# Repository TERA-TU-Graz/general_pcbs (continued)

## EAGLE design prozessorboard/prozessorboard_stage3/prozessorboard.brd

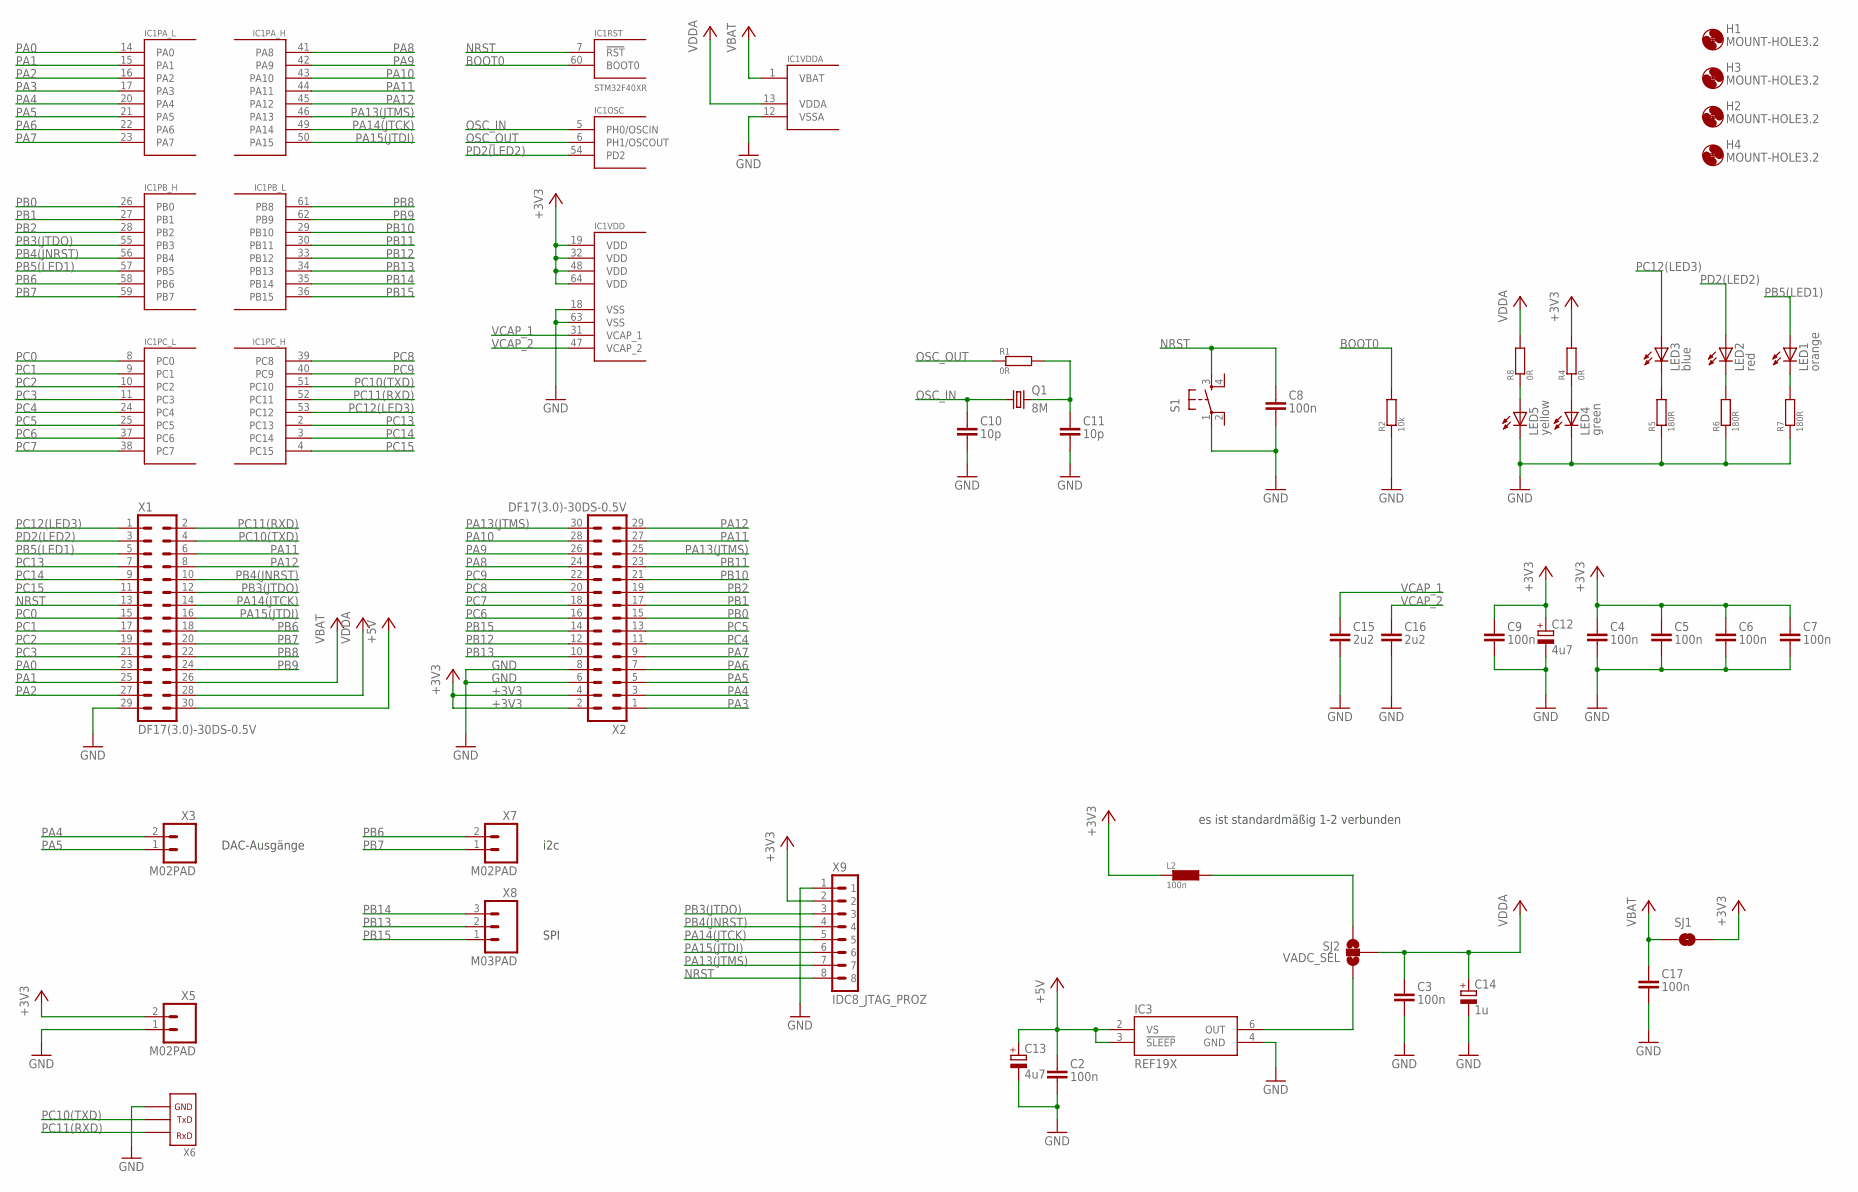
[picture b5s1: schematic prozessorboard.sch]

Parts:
C2, C3, C4, C5, C6, C7, C8, C9, C17: 100n; C0805
C10, C11: 10p; C0805
C12, C13: 4u7; CT3528
C14: 1u; CT3216
C15, C16: 2u2; C0805
H1, H2, H3, H4: MOUNT-HOLE3.2; 3,2
IC1: STM32F40XR; LQFP64
IC3: REF19X; SO08
L2: 100n; R0805
LED1: orange; CHIPLED_0805
LED2: red; CHIPLED_0805
LED3: blue; CHIPLED_0805
LED4: green; CHIPLED_0805
LED5: yellow; CHIPLED_0805
Q1: 8M; 0305
R1, R4, R8: 0R; R0805
R2: 10k; R0805
R5, R6, R7: 180R; R0805
S1: TAC_SWITCH; FSMJSMA
SJ1: SOLDERJUMPERNO; SJ_2S-NO
SJ2: VADC_SEL; SJ_3_PASTE1&2
X1, X2: DF17(3.0)-30DS-0.5V
X3, X5, X7: M02PAD; 1X02
X6: RS232V; 6410-03
X8: M03PAD; 1X03
X9: IDC8_JTAG_PROZ; 1X01

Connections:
+3V3: C4.2, C5.2, C6.2, C7.2, C9.2, C12.+, IC1.19 (VDD), IC1.32 (VDD), IC1.48 (VDD), IC1.64 (VDD), L2.1, R4.2, SJ1.2, X2.2, X2.4, X5.2, X9.2
+5V: C2.2, C13.+, IC3.2 (VS), IC3.3 (!SLEEP), X1.30
BOOT0: IC1.60 (BOOT0), R2.2
GND: C2.1, C3.1, C4.1, C5.1, C6.1, C7.1, C8.1, C9.1, C10.1, C11.1, C12.-, C13.-, C14.-, C15.1, C16.1, C17.1, IC1.12 (VSSA), IC1.18 (VSS), IC1.63 (VSS), IC3.4 (GND), LED4.C, LED5.C, R2.1, R5.1, R6.1, R7.1, S1.1, X1.29, X2.6, X2.8, X5.1, X6.1 (GND), X9.1
unnamed: C11.2, Q1.2, R1.2
unnamed: LED3.C, R5.2
unnamed: LED4.A, R4.1
unnamed: LED2.C, R6.2
unnamed: LED1.C, R7.2
unnamed: IC3.6 (OUT), SJ2.3
unnamed: LED5.A, R8.1
unnamed: L2.2, SJ2.1
NRST: C8.2, IC1.7 (!RST), S1.3, X1.13, X9.8
OSC_IN: C10.2, IC1.5 (PH0/OSCIN), Q1.1
OSC_OUT: IC1.6 (PH1/OSCOUT), R1.1
PA0: IC1.14 (PA0), X1.23
PA1: IC1.15 (PA1), X1.25
PA2: IC1.16 (PA2), X1.27
PA3: IC1.17 (PA3), X2.1
PA4: IC1.20 (PA4), X2.3, X3.2
PA5: IC1.21 (PA5), X2.5, X3.1
PA6: IC1.22 (PA6), X2.7
PA7: IC1.23 (PA7), X2.9
PA8: IC1.41 (PA8), X2.24
PA9: IC1.42 (PA9), X2.26
PA10: IC1.43 (PA10), X2.28
PA11: IC1.44 (PA11), X1.6, X2.27
PA12: IC1.45 (PA12), X1.8, X2.29
PA13(JTMS): IC1.46 (PA13), X2.25, X2.30, X9.7
PA14(JTCK): IC1.49 (PA14), X1.14, X9.5
PA15(JTDI): IC1.50 (PA15), X1.16, X9.6
PB0: IC1.26 (PB0), X2.15
PB1: IC1.27 (PB1), X2.17
PB2: IC1.28 (PB2), X2.19
PB3(JTDO): IC1.55 (PB3), X1.12, X9.3
PB4(JNRST): IC1.56 (PB4), X1.10, X9.4
PB5(LED1): IC1.57 (PB5), LED1.A, X1.5
PB6: IC1.58 (PB6), X1.18, X7.2
PB7: IC1.59 (PB7), X1.20, X7.1
PB8: IC1.61 (PB8), X1.22
PB9: IC1.62 (PB9), X1.24
PB10: IC1.29 (PB10), X2.21
PB11: IC1.30 (PB11), X2.23
PB12: IC1.33 (PB12), X2.12
PB13: IC1.34 (PB13), X2.10, X8.2
PB14: IC1.35 (PB14), X8.3
PB15: IC1.36 (PB15), X2.14, X8.1
PC0: IC1.8 (PC0), X1.15
PC1: IC1.9 (PC1), X1.17
PC2: IC1.10 (PC2), X1.19
PC3: IC1.11 (PC3), X1.21
PC4: IC1.24 (PC4), X2.11
PC5: IC1.25 (PC5), X2.13
PC6: IC1.37 (PC6), X2.16
PC7: IC1.38 (PC7), X2.18
PC8: IC1.39 (PC8), X2.20
PC9: IC1.40 (PC9), X2.22
PC10(TXD): IC1.51 (PC10), X1.4, X6.2 (TXD)
PC11(RXD): IC1.52 (PC11), X1.2, X6.3 (RXD)
PC12(LED3): IC1.53 (PC12), LED3.A, X1.1
PC13: IC1.2 (PC13), X1.7
PC14: IC1.3 (PC14), X1.9
PC15: IC1.4 (PC15), X1.11
PD2(LED2): IC1.54 (PD2), LED2.A, X1.3
VBAT: C17.2, IC1.1 (VBAT), SJ1.1, X1.26
VCAP_1: C15.2, IC1.31 (VCAP_1)
VCAP_2: C16.2, IC1.47 (VCAP_2)
VDDA: C3.2, C14.+, IC1.13 (VDDA), R8.2, SJ2.2, X1.28

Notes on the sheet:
es ist standardmäßig 1-2 verbunden
DAC-Ausgänge
SPI
i2c

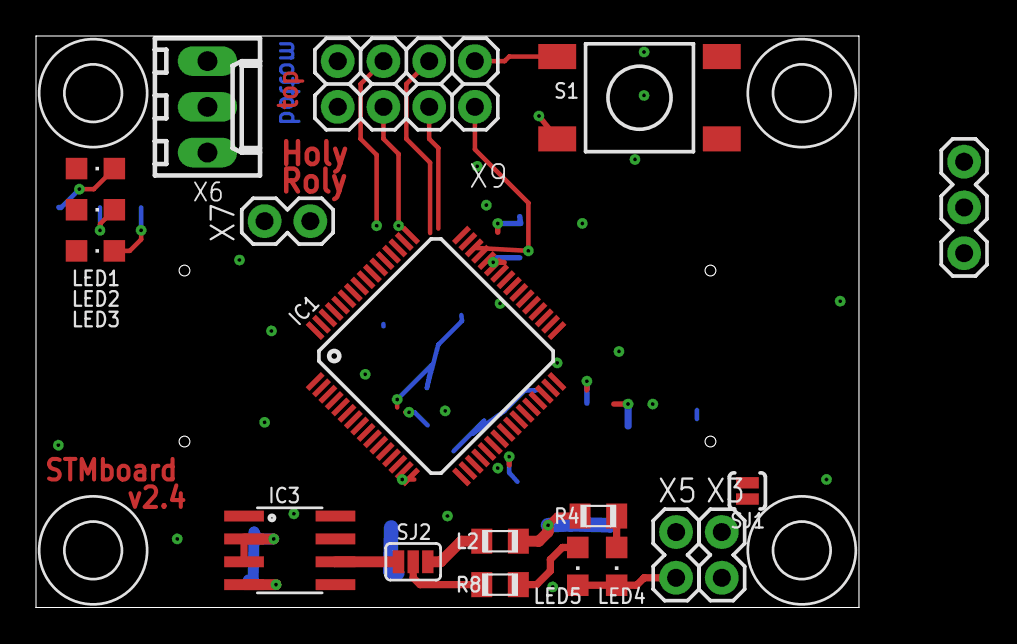
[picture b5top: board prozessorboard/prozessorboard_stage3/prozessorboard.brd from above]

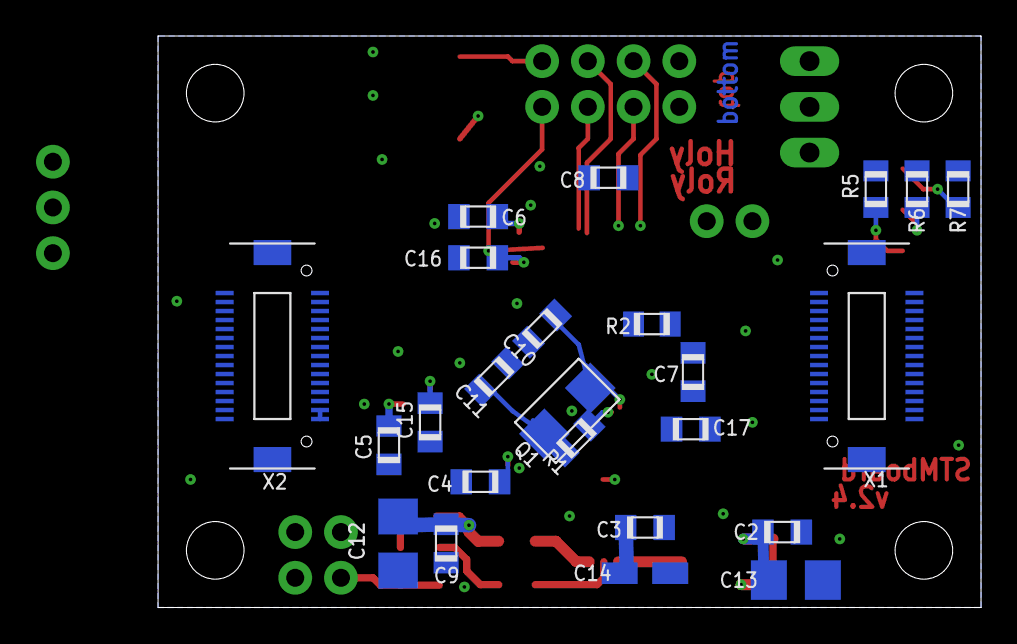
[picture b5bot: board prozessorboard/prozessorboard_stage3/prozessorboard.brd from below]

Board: 4 copper layers, 45.7 x 31.8 mm, 47 parts (24 on the bottom side), 68 nets.

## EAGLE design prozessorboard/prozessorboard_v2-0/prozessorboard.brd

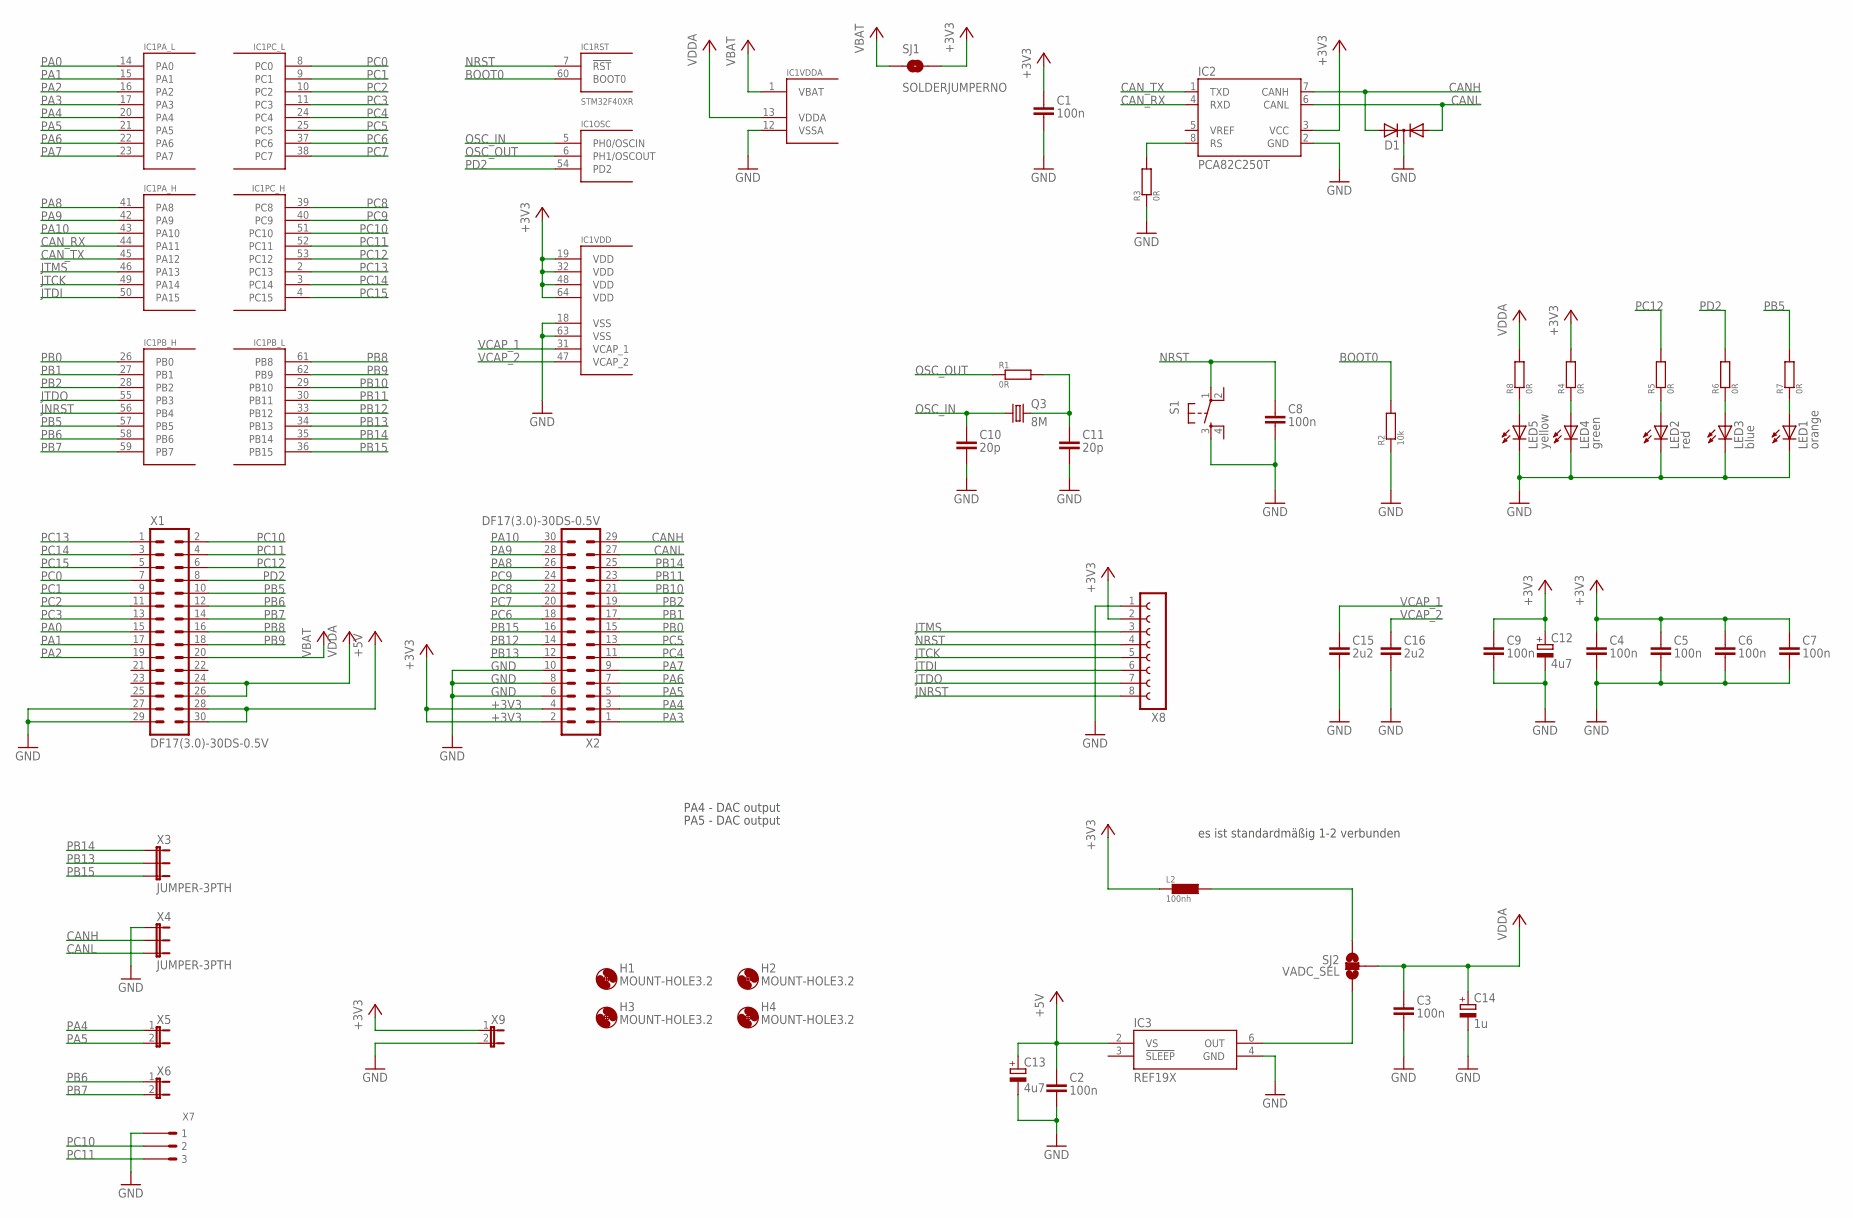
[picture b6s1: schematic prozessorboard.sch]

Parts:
C1, C2, C3, C4, C5, C6, C7, C8, C9: 100n; C0805
C10, C11: 20p; C0805
C12, C13: 4u7; SMC_C
C14: 1u; SMC_A
C15, C16: 2u2; C0805
D1: DIODE-2AC|CASOT23; SOT23
H1, H2, H3, H4: MOUNT-HOLE3.2; 3,2
IC1: STM32F40XR; LQFP64
IC2: PCA82C250T; SOIC-8
IC3: REF19X; SO08
L2: 100nh; R0805
LED1: orange; CHIPLED_0805
LED2: red; CHIPLED_0805
LED3: blue; CHIPLED_0805
LED4: green; CHIPLED_0805
LED5: yellow; CHIPLED_0805
Q3: 8M; 0305
R1, R3, R4, R5, R6, R7, R8: 0R; R0805
R2: 10k; R0805
S1: TAC_SWITCH; FSMJSMA
SJ1: SOLDERJUMPERNO; SJ_2S-NO
SJ2: VADC_SEL; SJ_3_PASTE1&2
X1, X2: DF17(3.0)-30DS-0.5V
X3, X4: JUMPER-3PTH; 1X03
X5, X6, X9: JUMPER-2PTH; 1X02
X7: 22-33; 6410-03
X8: FE08-1; FE08

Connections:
+3V3: C1.2, C4.2, C5.2, C6.2, C7.2, C9.2, C12.+, IC1.19 (VDD), IC1.32 (VDD), IC1.48 (VDD), IC1.64 (VDD), IC2.3 (VCC), L2.1, R4.2, SJ1.2, X2.2, X2.4, X8.2, X9.1
+5V: C2.2, C13.+, IC3.2 (VS), X1.28, X1.30
BOOT0: IC1.60 (BOOT0), R2.2
CANH: D1.2 (A2), IC2.7 (CANH), X2.29, X4.2
CANL: D1.1 (A1), IC2.6 (CANL), X2.27, X4.3
CAN_RX: IC1.44 (PA11), IC2.4 (RXD)
CAN_TX: IC1.45 (PA12), IC2.1 (TXD)
GND: C1.1, C2.1, C3.1, C4.1, C5.1, C6.1, C7.1, C8.1, C9.1, C10.1, C11.1, C12.-, C13.-, C14.-, C15.1, C16.1, D1.3 (C), IC1.12 (VSSA), IC1.18 (VSS), IC1.63 (VSS), IC2.2 (GND), IC3.4 (GND), LED1.C, LED2.C, LED3.C, LED4.C, LED5.C, R2.1, R3.1, S1.3, X1.27, X1.29, X2.6, X2.8, X2.10, X4.1, X7.1, X8.1, X9.2
JNRST: IC1.56 (PB4), X8.8
JTCK: IC1.49 (PA14), X8.5
JTDI: IC1.50 (PA15), X8.6
JTDO: IC1.55 (PB3), X8.7
JTMS: IC1.46 (PA13), X8.3
unnamed: C11.2, Q3.2, R1.2
unnamed: LED1.A, R7.1
unnamed: LED4.A, R4.1
unnamed: LED2.A, R5.1
unnamed: LED3.A, R6.1
unnamed: IC2.8 (RS), R3.2
unnamed: IC3.6 (OUT), SJ2.3
unnamed: LED5.A, R8.1
unnamed: L2.2, SJ2.1
NRST: C8.2, IC1.7 (!RST), S1.1, X8.4
OSC_IN: C10.2, IC1.5 (PH0/OSCIN), Q3.1
OSC_OUT: IC1.6 (PH1/OSCOUT), R1.1
PA0: IC1.14 (PA0), X1.15
PA1: IC1.15 (PA1), X1.17
PA2: IC1.16 (PA2), X1.19
PA3: IC1.17 (PA3), X2.1
PA4: IC1.20 (PA4), X2.3, X5.1
PA5: IC1.21 (PA5), X2.5, X5.2
PA6: IC1.22 (PA6), X2.7
PA7: IC1.23 (PA7), X2.9
PA8: IC1.41 (PA8), X2.26
PA9: IC1.42 (PA9), X2.28
PA10: IC1.43 (PA10), X2.30
PB0: IC1.26 (PB0), X2.15
PB1: IC1.27 (PB1), X2.17
PB2: IC1.28 (PB2), X2.19
PB5: IC1.57 (PB5), R7.2, X1.10
PB6: IC1.58 (PB6), X1.12, X6.1
PB7: IC1.59 (PB7), X1.14, X6.2
PB8: IC1.61 (PB8), X1.16
PB9: IC1.62 (PB9), X1.18
PB10: IC1.29 (PB10), X2.21
PB11: IC1.30 (PB11), X2.23
PB12: IC1.33 (PB12), X2.14
PB13: IC1.34 (PB13), X2.12, X3.2
PB14: IC1.35 (PB14), X2.25, X3.1
PB15: IC1.36 (PB15), X2.16, X3.3
PC0: IC1.8 (PC0), X1.7
PC1: IC1.9 (PC1), X1.9
PC2: IC1.10 (PC2), X1.11
PC3: IC1.11 (PC3), X1.13
PC4: IC1.24 (PC4), X2.11
PC5: IC1.25 (PC5), X2.13
PC6: IC1.37 (PC6), X2.18
PC7: IC1.38 (PC7), X2.20
PC8: IC1.39 (PC8), X2.22
PC9: IC1.40 (PC9), X2.24
PC10: IC1.51 (PC10), X1.2, X7.2
PC11: IC1.52 (PC11), X1.4, X7.3
PC12: IC1.53 (PC12), R5.2, X1.6
PC13: IC1.2 (PC13), X1.1
PC14: IC1.3 (PC14), X1.3
PC15: IC1.4 (PC15), X1.5
PD2: IC1.54 (PD2), R6.2, X1.8
VBAT: IC1.1 (VBAT), SJ1.1, X1.20
VCAP_1: C15.2, IC1.31 (VCAP_1)
VCAP_2: C16.2, IC1.47 (VCAP_2)
VDDA: C3.2, C14.+, IC1.13 (VDDA), R8.2, SJ2.2, X1.24, X1.26

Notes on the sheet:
PA4 - DAC output
PA5 - DAC output
es ist standardmäßig 1-2 verbunden

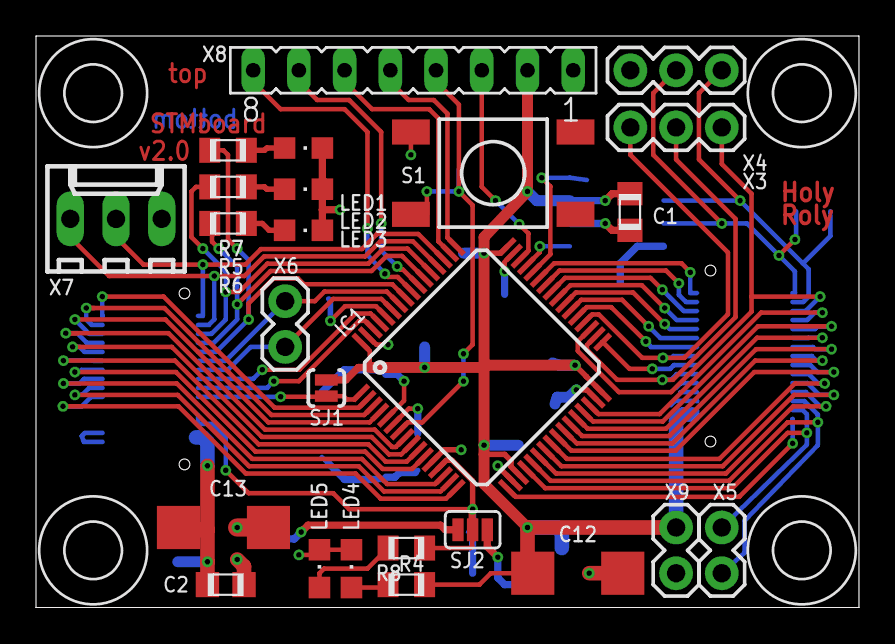
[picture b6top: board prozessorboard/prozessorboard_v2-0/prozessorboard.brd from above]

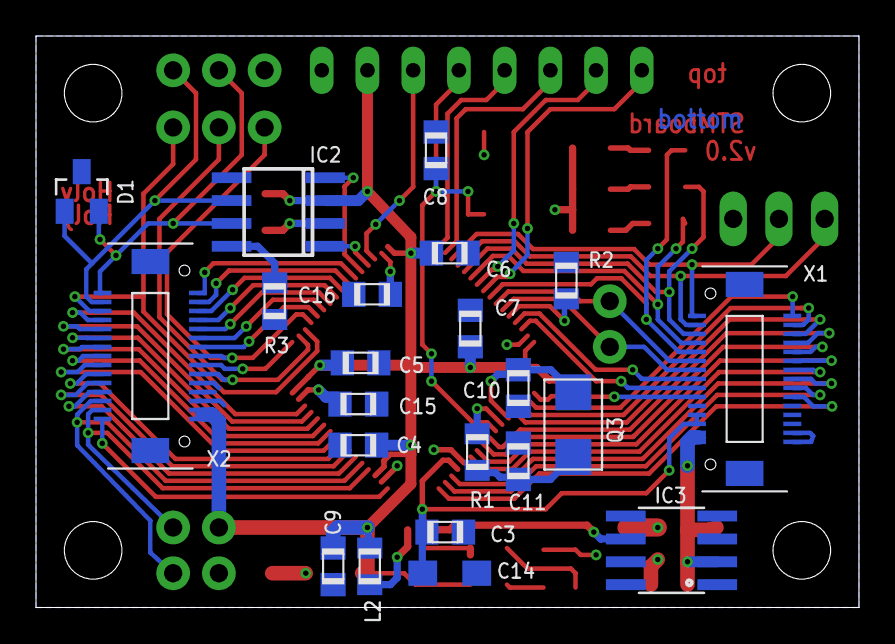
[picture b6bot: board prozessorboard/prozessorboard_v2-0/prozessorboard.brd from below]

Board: 2 copper layers, 45.7 x 31.8 mm, 51 parts (22 on the bottom side), 71 nets.

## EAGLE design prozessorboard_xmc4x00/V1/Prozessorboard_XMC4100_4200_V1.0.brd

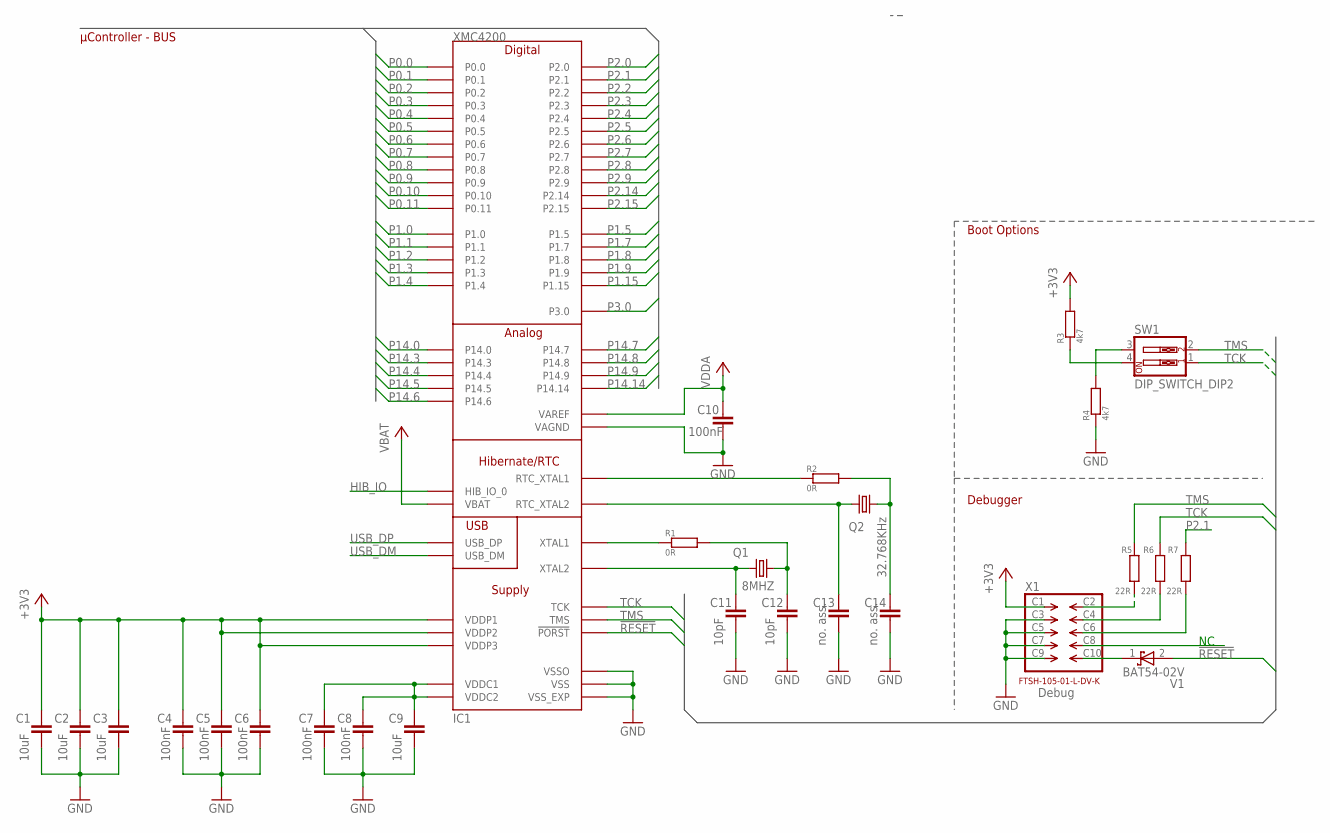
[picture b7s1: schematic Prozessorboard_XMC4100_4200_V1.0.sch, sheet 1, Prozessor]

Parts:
C1, C2, C3, C9: 10uF; C0805; MPN 1825002-1
C4, C5, C6, C7, C8, C10: 100nF; C0805
C11, C12: 10pF; C0805; MPN 1825002-1
C13, C14: no. ass.; C0805; MPN 1825002-1
IC1: XMC4200; INF-PG-LQFP-64-19-5800X5800T57PRIMARY
Q1: 8MHZ; 0305+1MM
Q2: 32.768KHz; 0305+1MM
R1, R2: 0R; R0805@1
R3, R4: 4k7; R0805@1
R5, R6, R7: 22R; R0805@1
SW1: DIP_SWITCH_DIP2; DIPSWITCH-02
V1: BAT54-02V; SC79
X1: Debug; SMD_10PIN_2ROW_1.27MM_SAMTEC

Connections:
!RESET: IC1.43 (!PORST), V1.2 (A); also elsewhere on the board
+3V3: C1.2, C2.2, C3.2, C4.2, C5.2, C6.2, IC1.8 (VDDP1), IC1.38 (VDDP2), IC1.56 (VDDP3), R3.2, X1.C1; also elsewhere on the board
GND: C1.1, C2.1, C3.1, C4.1, C5.1, C6.1, C7.1, C8.1, C9.1, C10.1, C11.1, C12.1, C13.1, C14.1, IC1.21 (VAGND), IC1.37 (VSS), IC1.41 (VSSO), IC1.65 (VSS_EXP), R4.1, X1.C3, X1.C5, X1.C7, X1.C9; also elsewhere on the board
HIB_IO: IC1.10 (HIB_IO_0); also elsewhere on the board
unnamed: C11.2, IC1.40 (XTAL2), Q1.2
unnamed: V1.1 (C), X1.C10
unnamed: IC1.39 (XTAL1), R1.1
unnamed: C7.2, C8.2, C9.2, IC1.9 (VDDC1), IC1.42 (VDDC2)
unnamed: C13.2, IC1.12 (RTC_XTAL2), Q2.2
unnamed: IC1.11 (RTC_XTAL1), R2.1
unnamed: C14.2, Q2.1, R2.2
unnamed: C12.2, Q1.1, R1.2
unnamed: R5.1, X1.C2
unnamed: R6.1, X1.C4
unnamed: R7.1, X1.C6
unnamed: R3.1, SW1.4
unnamed: R4.2, SW1.3
P0.0: IC1.2 (P0.0); also elsewhere on the board
P0.1: IC1.1 (P0.1); also elsewhere on the board
P0.2: IC1.64 (P0.2); also elsewhere on the board
P0.3: IC1.63 (P0.3); also elsewhere on the board
P0.4: IC1.62 (P0.4); also elsewhere on the board
P0.5: IC1.61 (P0.5); also elsewhere on the board
P0.6: IC1.60 (P0.6); also elsewhere on the board
P0.7: IC1.58 (P0.7); also elsewhere on the board
P0.8: IC1.57 (P0.8); also elsewhere on the board
P0.9: IC1.4 (P0.9); also elsewhere on the board
P0.10: IC1.3 (P0.10); also elsewhere on the board
P0.11: IC1.59 (P0.11); also elsewhere on the board
P1.0: IC1.52 (P1.0); also elsewhere on the board
P1.1: IC1.51 (P1.1); also elsewhere on the board
P1.2: IC1.50 (P1.2); also elsewhere on the board
P1.3: IC1.49 (P1.3); also elsewhere on the board
P1.4: IC1.48 (P1.4); also elsewhere on the board
P1.5: IC1.47 (P1.5); also elsewhere on the board
P1.7: IC1.55 (P1.7); also elsewhere on the board
P1.8: IC1.54 (P1.8); also elsewhere on the board
P1.9: IC1.53 (P1.9); also elsewhere on the board
P1.15: IC1.46 (P1.15); also elsewhere on the board
P2.0: IC1.34 (P2.0); also elsewhere on the board
P2.1: IC1.33 (P2.1), R7.2
P2.2: IC1.32 (P2.2); also elsewhere on the board
P2.3: IC1.31 (P2.3); also elsewhere on the board
P2.4: IC1.30 (P2.4); also elsewhere on the board
P2.5: IC1.29 (P2.5); also elsewhere on the board
P2.6: IC1.36 (P2.6); also elsewhere on the board
P2.7: IC1.35 (P2.7); also elsewhere on the board
P2.8: IC1.28 (P2.8); also elsewhere on the board
P2.9: IC1.27 (P2.9); also elsewhere on the board
P2.14: IC1.26 (P2.14); also elsewhere on the board
P2.15: IC1.25 (P2.15); also elsewhere on the board
P3.0: IC1.5 (P3.0); also elsewhere on the board
P14.0: IC1.20 (P14.0); also elsewhere on the board
P14.3: IC1.19 (P14.3); also elsewhere on the board
P14.4: IC1.18 (P14.4); also elsewhere on the board
P14.5: IC1.17 (P14.5); also elsewhere on the board
P14.6: IC1.16 (P14.6); also elsewhere on the board
P14.7: IC1.15 (P14.7); also elsewhere on the board
P14.8: IC1.24 (P14.8); also elsewhere on the board
P14.9: IC1.23 (P14.9); also elsewhere on the board
P14.14: IC1.14 (P14.14); also elsewhere on the board
TCK: IC1.45 (TCK), R6.2, SW1.1
TMS: IC1.44 (TMS), R5.2, SW1.2
USB_DM: IC1.6 (USB_DM); also elsewhere on the board
USB_DP: IC1.7 (USB_DP); also elsewhere on the board
VBAT: IC1.13 (VBAT); also elsewhere on the board
VDDA: C10.2, IC1.22 (VAREF); also elsewhere on the board

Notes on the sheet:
Debugger
Boot Options
µController - BUS

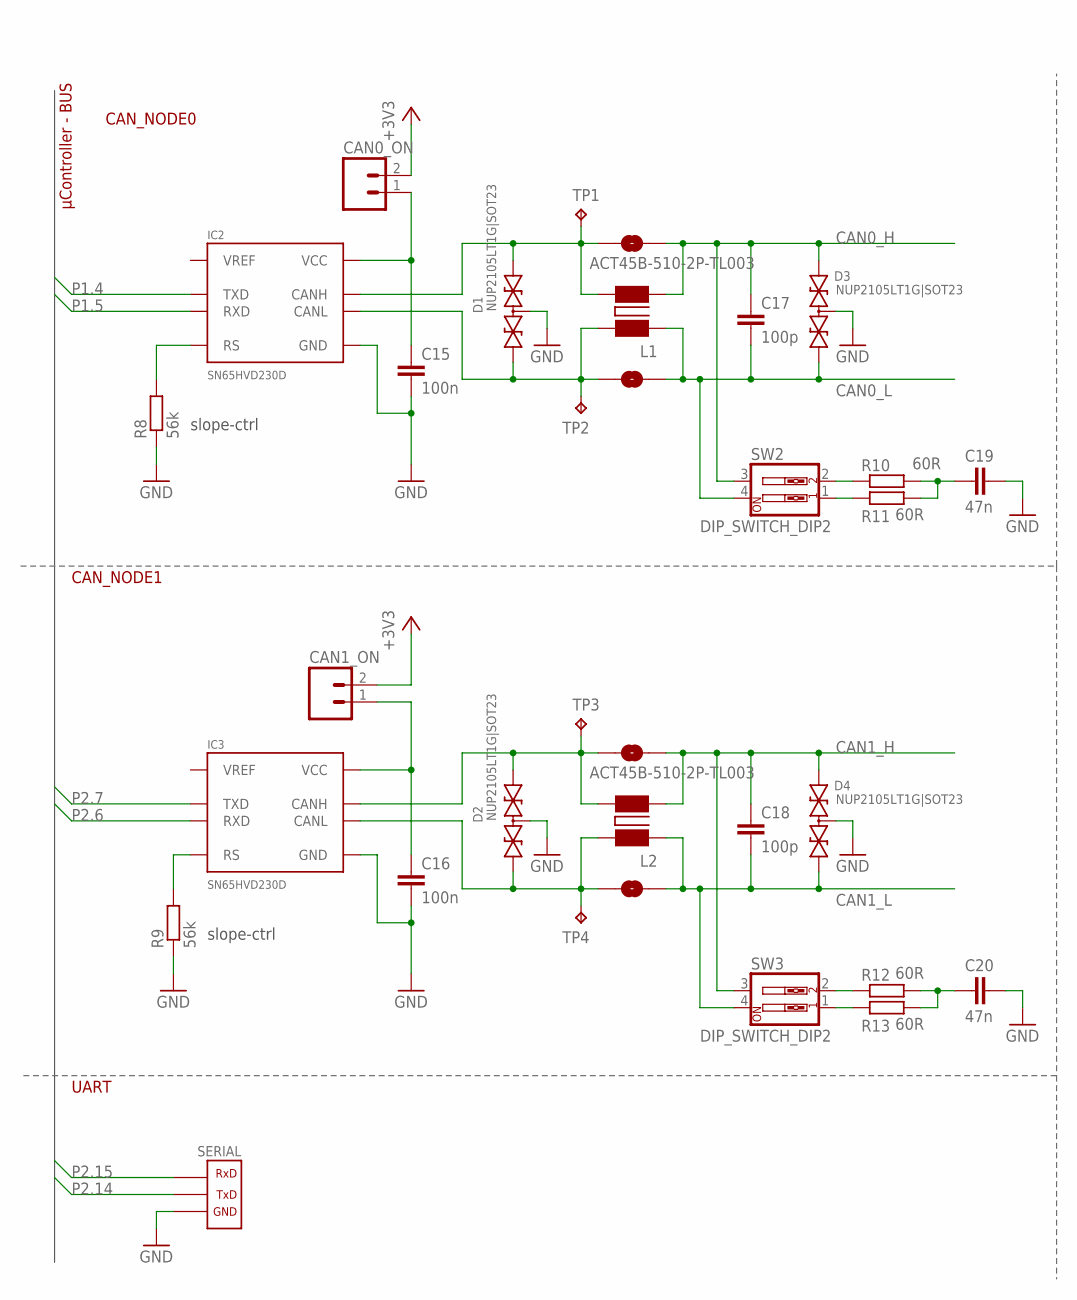
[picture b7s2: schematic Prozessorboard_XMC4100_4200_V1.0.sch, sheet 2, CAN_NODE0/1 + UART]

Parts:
C15, C16: 100n; C0805
C17, C18: 100p; C0805
C19, C20: 47n; C0805
CAN0_ON, CAN1_ON: M02PAD; 1X02
D1, D2, D3, D4: NUP2105LT1G|SOT23; SOT23
IC2, IC3: SN65HVD230D; SO08
L1, L2: ACT45B-510-2P-TL003; ACT45B
R8, R9: 56k; R0805
R10, R11, R12, R13: 60R; R0805
SERIAL: RS232V; 6410-03
SJ1, SJ2, SJ3, SJ4: SOLDERJUMPERNO; SJ_2S-NO
SW2, SW3: DIP_SWITCH_DIP2; DIPSWITCH-02
TP1, TP2, TP3, TP4: TPPAD1-13; P1-13

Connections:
+3V3: CAN0_ON.2, CAN1_ON.2; also elsewhere on the board
CAN0_H: C17.1, D3.2, L1.P$1 (1), SJ1.2, SW2.3; also elsewhere on the board
CAN0_L: C17.2, D3.1, L1.P$3 (3), SJ2.2, SW2.4; also elsewhere on the board
CAN1_H: C18.1, D4.2, L2.P$1 (1), SJ3.2, SW3.3; also elsewhere on the board
CAN1_L: C18.2, D4.1, L2.P$3 (3), SJ4.2, SW3.4; also elsewhere on the board
GND: C15.2, C16.2, C19.2, C20.2, D1.3, D2.3, D3.3, D4.3, IC2.2 (GND), IC3.2 (GND), R8.1, R9.1, SERIAL.1 (GND); also elsewhere on the board
unnamed: R10.1, SW2.2
unnamed: R12.1, SW3.2
unnamed: R13.1, SW3.1
unnamed: IC3.8 (RS), R9.2
unnamed: C16.1, CAN1_ON.1, IC3.3 (VCC)
unnamed: D2.2, IC3.7 (CANH), L2.P$2 (2), SJ3.1, TP3.TP
unnamed: C15.1, CAN0_ON.1, IC2.3 (VCC)
unnamed: D2.1, IC3.6 (CANL), L2.P$4 (4), SJ4.1, TP4.TP
unnamed: IC2.8 (RS), R8.2
unnamed: R11.1, SW2.1
unnamed: C19.1, R10.2, R11.2
unnamed: D1.2, IC2.7 (CANH), L1.P$2 (2), SJ1.1, TP1.TP
unnamed: D1.1, IC2.6 (CANL), L1.P$4 (4), SJ2.1, TP2.TP
unnamed: C20.1, R12.2, R13.2
P1.4: IC2.1 (TXD); also elsewhere on the board
P1.5: IC2.4 (RXD); also elsewhere on the board
P2.6: IC3.4 (RXD); also elsewhere on the board
P2.7: IC3.1 (TXD); also elsewhere on the board
P2.14: SERIAL.2 (TXD); also elsewhere on the board
P2.15: SERIAL.3 (RXD); also elsewhere on the board

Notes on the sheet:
CAN_NODE0
slope-ctrl
CAN_NODE1
µController - BUS
UART

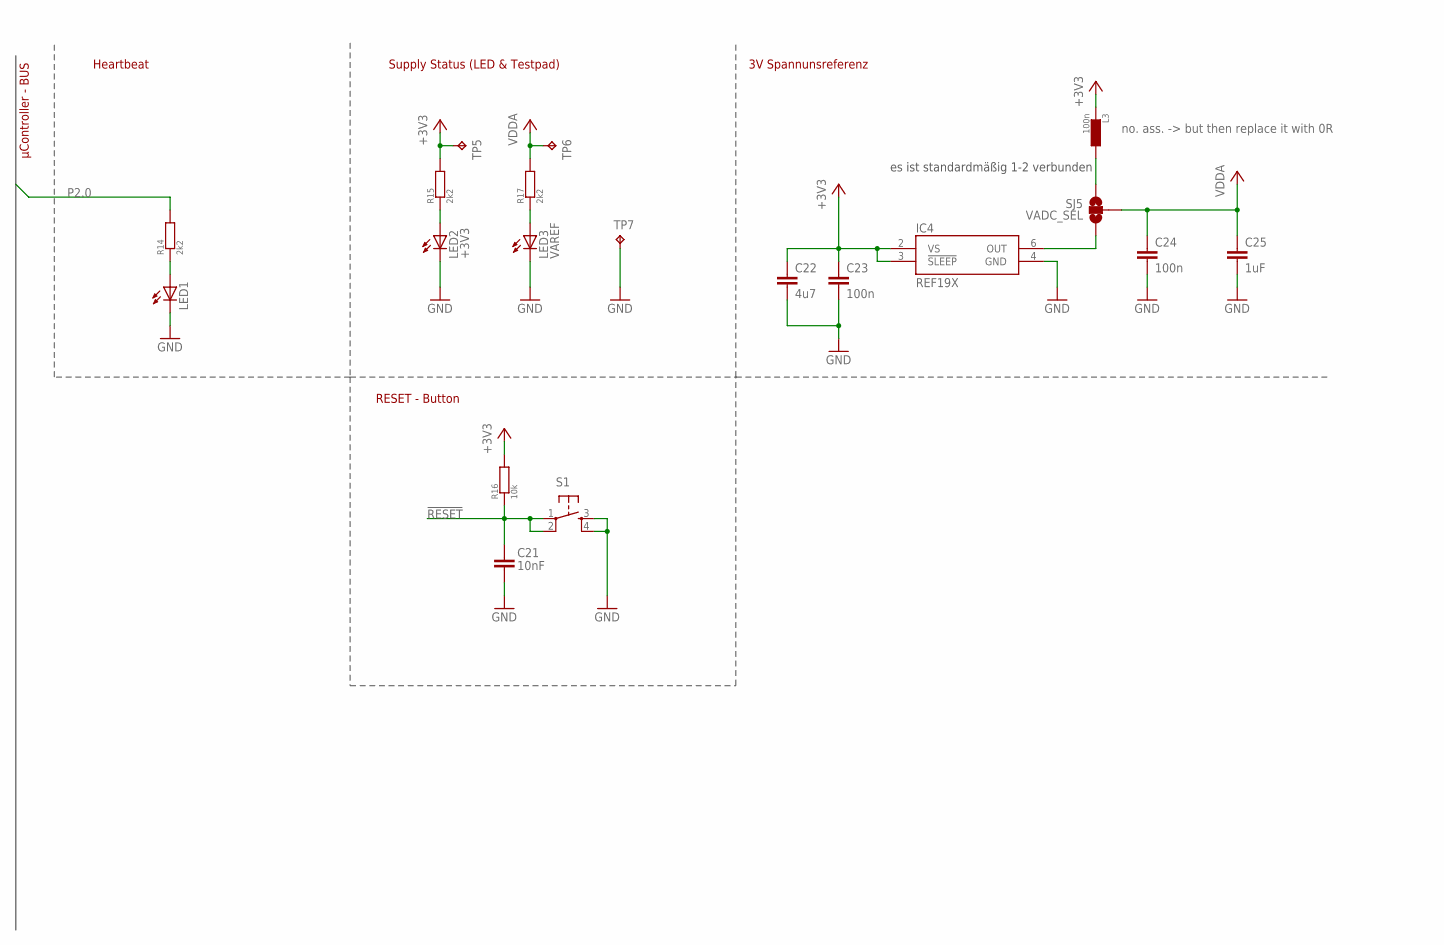
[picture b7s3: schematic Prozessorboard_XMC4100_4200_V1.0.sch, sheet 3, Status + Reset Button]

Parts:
C21: 10nF; C0805
C22: 4u7; 0805
C23, C24: 100n; 0805
C25: 1uF; 0805
IC4: REF19X; SO08
L3: 100n; R0805
LED1: LEDCHIPLED_0805; CHIPLED_0805
LED2: +3V3; CHIPLED_0805
LED3: VAREF; CHIPLED_0805
R14, R15, R17: 2k2; R0805@1
R16: 10k; R0805@1
S1: TAC_SWITCH; FSMJSMA
SJ5: VADC_SEL; SJ_3_PASTE1&2
TP5, TP6, TP7: TPPAD1-13; P1-13

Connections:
!RESET: C21.2, R16.1, S1.1, S1.2; also elsewhere on the board
+3V3: C22.1, C23.1, IC4.2 (VS), IC4.3 (!SLEEP), L3.1, R15.2, R16.2, TP5.TP; also elsewhere on the board
GND: C21.1, C22.2, C23.2, C24.2, C25.2, IC4.4 (GND), LED1.C, LED2.C, LED3.C, S1.3, S1.4, TP7.TP; also elsewhere on the board
unnamed: LED1.A, R14.1
unnamed: LED2.A, R15.1
unnamed: LED3.A, R17.1
unnamed: L3.2, SJ5.1
unnamed: IC4.6 (OUT), SJ5.3
P2.0: R14.2; also elsewhere on the board
VDDA: C24.1, C25.1, R17.2, SJ5.2, TP6.TP; also elsewhere on the board

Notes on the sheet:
Heartbeat
Supply Status (LED & Testpad)
RESET - Button
µController - BUS
es ist standardmäßig 1-2 verbunden
3V Spannunsreferenz
no. ass. -> but then replace it with 0R

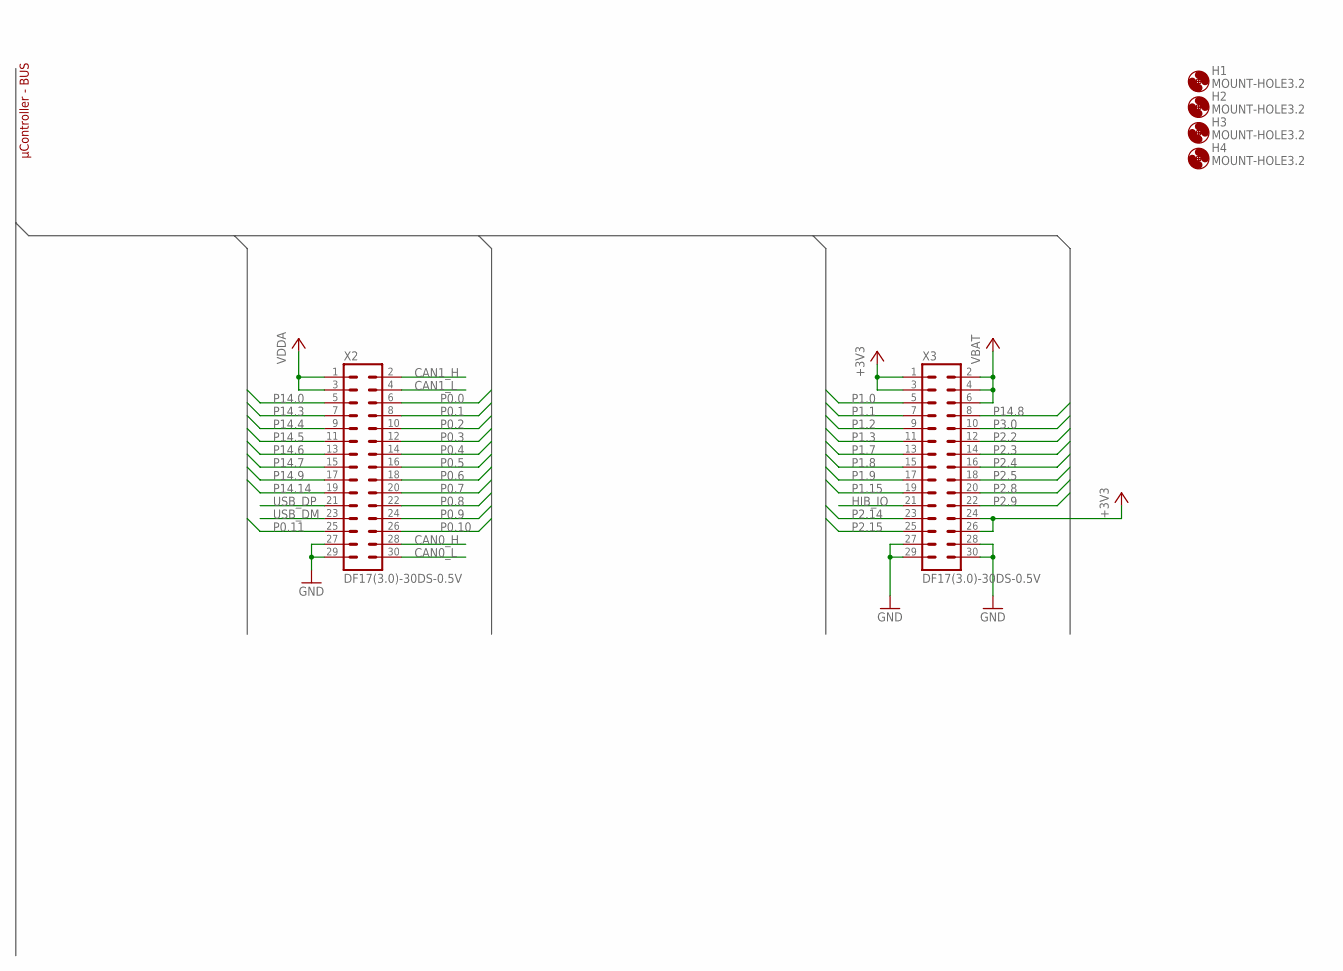
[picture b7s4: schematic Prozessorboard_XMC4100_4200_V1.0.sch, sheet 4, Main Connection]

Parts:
H1, H2, H3, H4: MOUNT-HOLE3.2; 3,2
X2, X3: DF17(3.0)-30DS-0.5V

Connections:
+3V3: X3.1, X3.3, X3.24, X3.26; also elsewhere on the board
CAN0_H: X2.28; also elsewhere on the board
CAN0_L: X2.30; also elsewhere on the board
CAN1_H: X2.2; also elsewhere on the board
CAN1_L: X2.4; also elsewhere on the board
GND: X2.27, X2.29, X3.27, X3.28, X3.29, X3.30; also elsewhere on the board
HIB_IO: X3.21; also elsewhere on the board
P0.0: X2.6; also elsewhere on the board
P0.1: X2.8; also elsewhere on the board
P0.2: X2.10; also elsewhere on the board
P0.3: X2.12; also elsewhere on the board
P0.4: X2.14; also elsewhere on the board
P0.5: X2.16; also elsewhere on the board
P0.6: X2.18; also elsewhere on the board
P0.7: X2.20; also elsewhere on the board
P0.8: X2.22; also elsewhere on the board
P0.9: X2.24; also elsewhere on the board
P0.10: X2.26; also elsewhere on the board
P0.11: X2.25; also elsewhere on the board
P1.0: X3.5; also elsewhere on the board
P1.1: X3.7; also elsewhere on the board
P1.2: X3.9; also elsewhere on the board
P1.3: X3.11; also elsewhere on the board
P1.7: X3.13; also elsewhere on the board
P1.8: X3.15; also elsewhere on the board
P1.9: X3.17; also elsewhere on the board
P1.15: X3.19; also elsewhere on the board
P2.2: X3.12; also elsewhere on the board
P2.3: X3.14; also elsewhere on the board
P2.4: X3.16; also elsewhere on the board
P2.5: X3.18; also elsewhere on the board
P2.8: X3.20; also elsewhere on the board
P2.9: X3.22; also elsewhere on the board
P2.14: X3.23; also elsewhere on the board
P2.15: X3.25; also elsewhere on the board
P3.0: X3.10; also elsewhere on the board
P14.0: X2.5; also elsewhere on the board
P14.3: X2.7; also elsewhere on the board
P14.4: X2.9; also elsewhere on the board
P14.5: X2.11; also elsewhere on the board
P14.6: X2.13; also elsewhere on the board
P14.7: X2.15; also elsewhere on the board
P14.8: X3.8; also elsewhere on the board
P14.9: X2.17; also elsewhere on the board
P14.14: X2.19; also elsewhere on the board
USB_DM: X2.23; also elsewhere on the board
USB_DP: X2.21; also elsewhere on the board
VBAT: X3.2, X3.4, X3.6; also elsewhere on the board
VDDA: X2.1, X2.3; also elsewhere on the board

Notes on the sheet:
µController - BUS
